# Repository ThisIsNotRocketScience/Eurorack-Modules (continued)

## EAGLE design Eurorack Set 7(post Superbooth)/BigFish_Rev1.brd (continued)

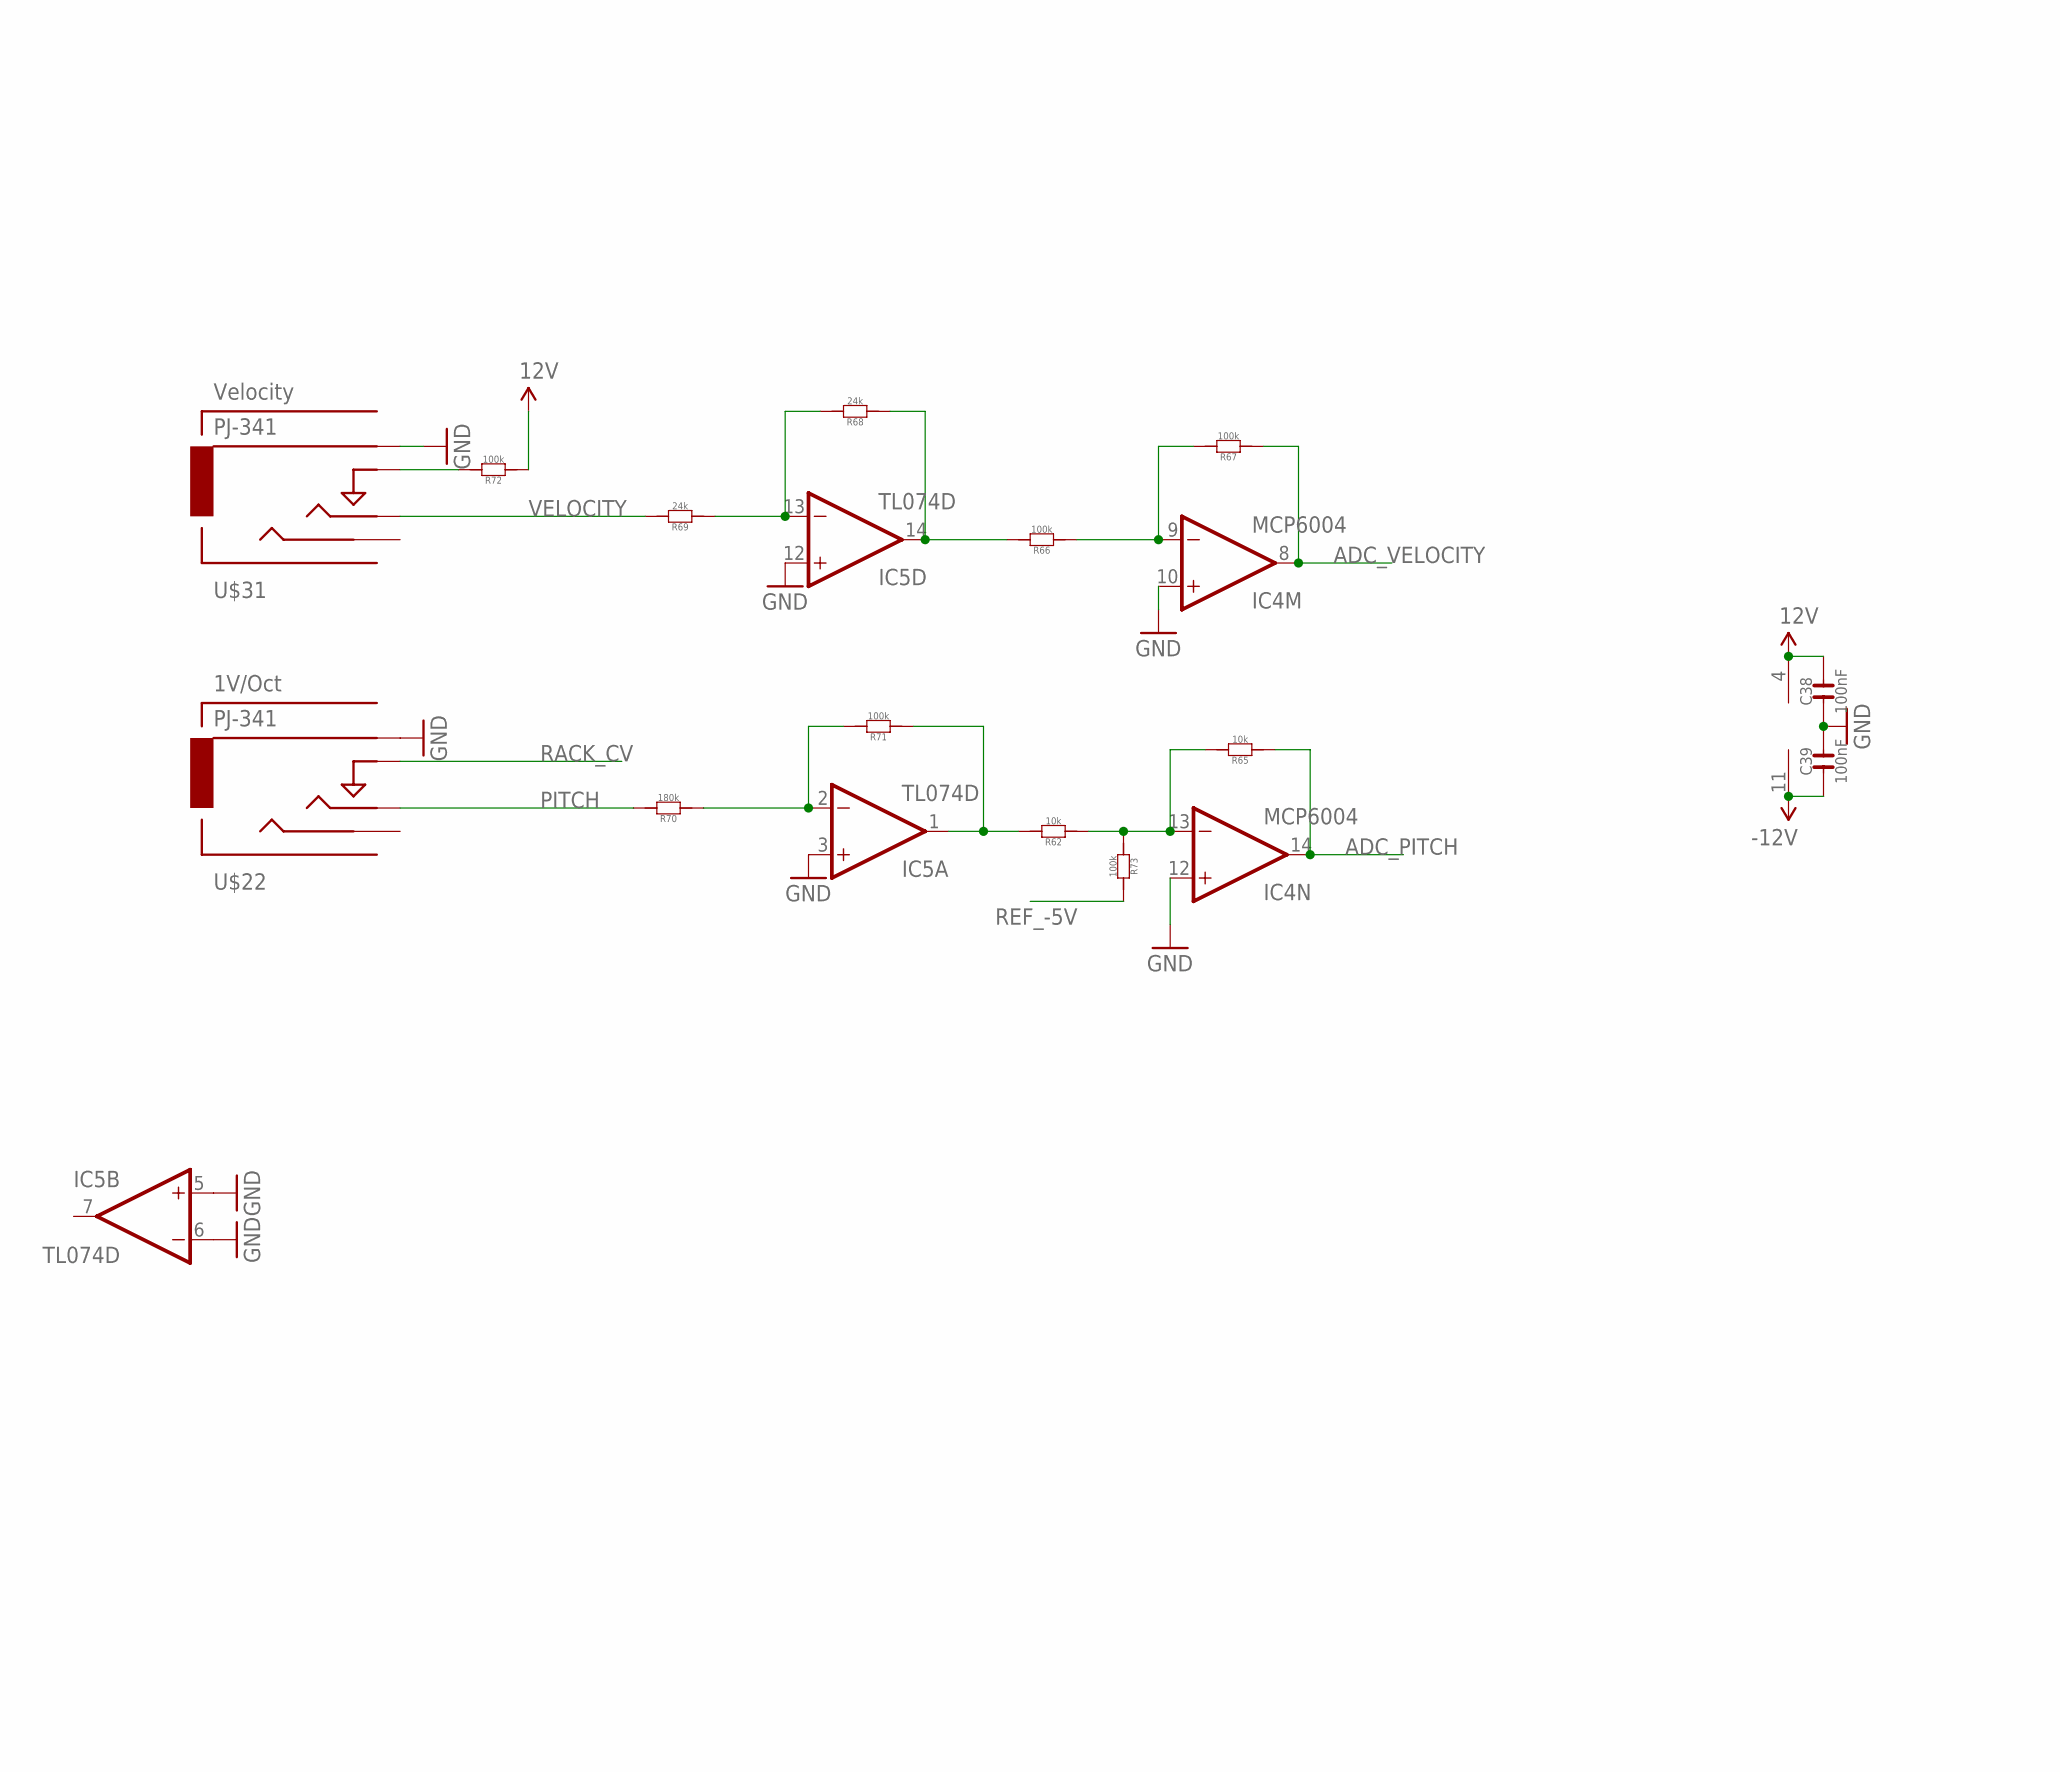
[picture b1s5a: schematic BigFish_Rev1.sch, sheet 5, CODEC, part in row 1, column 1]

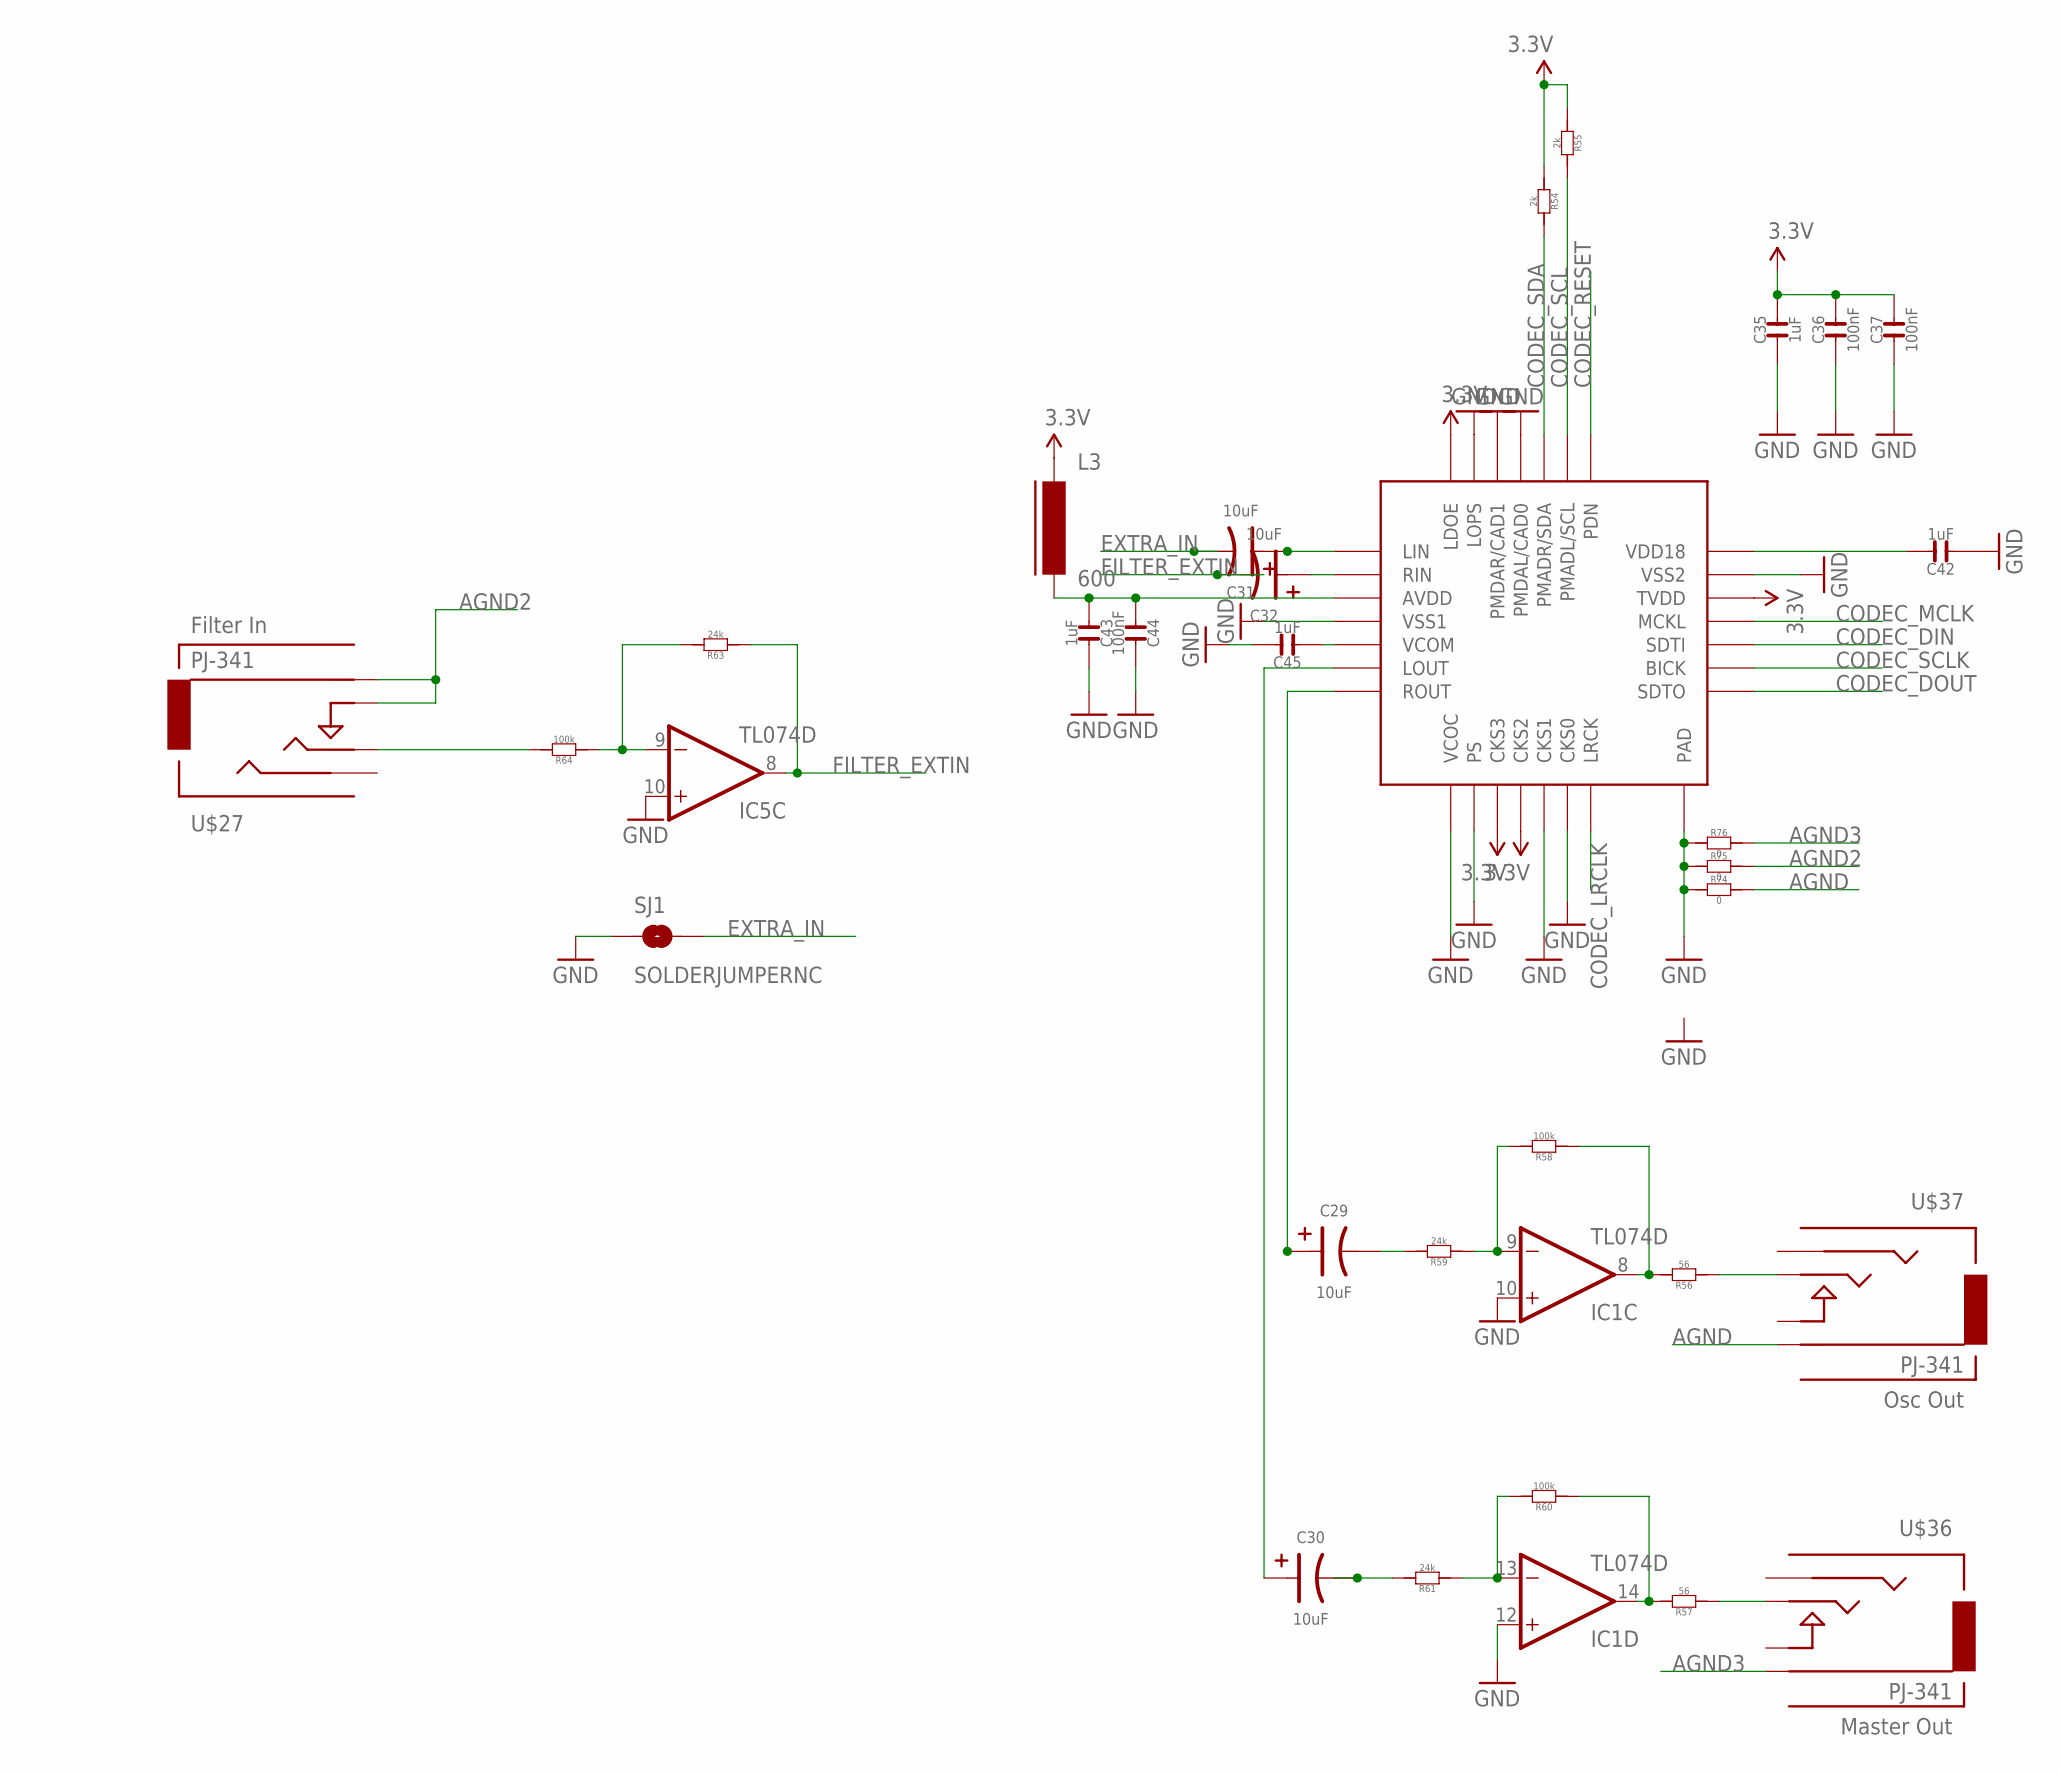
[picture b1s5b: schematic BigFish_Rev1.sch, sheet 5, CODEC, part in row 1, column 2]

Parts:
C29, C30, C31, C32: 10uF; AVX-A; MPN TAJB106K020RNJ
C35, C42, C43, C45: 1uF; C0603
C36, C37, C38, C39, C44: 100nF; C0603
IC1, IC5: TL074D; SO14
IC4: MCP6004; SO14; MPN MCP6004-I/SL.
L3: 600; FB603
R54, R55: 2k; R0603
R56, R57: 56; R0603
R58, R60, R64, R66, R67, R71, R72, R73: 100k; R0603
R59, R61, R63, R68, R69: 24k; R0603
R62, R65: 10k; R0603
R70: 180k; R0603
R74, R75, R76: 0; R0603
SJ1: SOLDERJUMPERNC; SJ_2S
U$22, U$27, U$31: PJ-341; 3.5MM-JACK-SWITCH-13MM-INPUT
U$36, U$37: PJ-341; 3.5MM-JACK-SWITCH-13MM-OUTPUT
U$48: AK4558; QFN28

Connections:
3.3V: C35.2, C36.2, C37.2, L3.1, R54.2, R55.2, U$48.P$3 (CKS3), U$48.P$4 (CKS2), U$48.P$12 (TVDD), U$48.P$21 (LDOE); also elsewhere on the board
3.3VAUDIO1: C43.1, C44.1, L3.2, U$48.P$24 (AVDD)
12V: C38.2, IC5.4 (V+), R72.1; also elsewhere on the board
-12V: C39.1, IC5.11 (V-); also elsewhere on the board
ADC_PITCH: IC4.14 (OUT), R65.1; also elsewhere on the board
ADC_VELOCITY: IC4.8 (OUT), R67.1; also elsewhere on the board
AGND: R74.1, U$37.RING@3 (RING)
AGND2: R75.1, U$27.RING@3 (RING), U$27.SWITCH@3 (SWITCH)
AGND3: R76.1, U$36.RING@3 (RING)
CODEC_DIN: U$48.P$10 (SDTI); also elsewhere on the board
CODEC_DOUT: U$48.P$8 (SDTO); also elsewhere on the board
CODEC_LRCLK: U$48.P$7 (LRCK); also elsewhere on the board
CODEC_MCLK: U$48.P$11 (MCKL); also elsewhere on the board
CODEC_RESET: U$48.P$15 (PDN); also elsewhere on the board
CODEC_SCL: R55.1, U$48.P$16 (PMADL/SCL); also elsewhere on the board
CODEC_SCLK: U$48.P$9 (BICK); also elsewhere on the board
CODEC_SDA: R54.1, U$48.P$17 (PMADR/SDA); also elsewhere on the board
EXTRA_IN: C31.- (2), SJ1.2
FILTER_EXTIN: C32.- (2), IC5.8 (OUT), R63.1
GND: C35.1, C36.1, C37.1, C38.1, C39.2, C42.1, C43.2, C44.2, C45.2, IC1.10 (+IN), IC1.12 (+IN), IC4.10 (+IN), IC4.12 (+IN), IC5.3 (+IN), IC5.5 (+IN), IC5.6 (-IN), IC5.10 (+IN), IC5.12 (+IN), R74.2, R75.2, R76.2, SJ1.1, U$22.RING@3 (RING), U$31.RING@3 (RING), U$48.P$1 (VCOC), U$48.P$2 (PS), U$48.P$5 (CKS1), U$48.P$6 (CKS0), U$48.P$13 (VSS2), U$48.P$18 (PMDAL/CAD0), U$48.P$19 (PMDAR/CAD1), U$48.P$20 (LOPS), U$48.P$25 (VSS1), U$48.PAD; also elsewhere on the board
unnamed: C32.+ (1), U$48.P$23 (RIN)
unnamed: C29.+ (1), U$48.P$28 (ROUT)
unnamed: C30.+ (1), U$48.P$27 (LOUT)
unnamed: C31.+ (1), U$48.P$22 (LIN)
unnamed: R64.2, U$27.TIP@3 (TIP)
unnamed: IC5.2 (-IN), R70.1, R71.2
unnamed: IC5.1 (OUT), R62.2, R71.1
unnamed: C30.- (2), R61.2
unnamed: IC1.8 (OUT), R56.2, R58.1
unnamed: IC1.14 (OUT), R57.2, R60.1
unnamed: IC1.13 (-IN), R60.2, R61.1
unnamed: IC5.13 (-IN), R68.2, R69.1
unnamed: R57.1, U$36.TIP@3 (TIP)
unnamed: C29.- (2), R59.2
unnamed: IC1.9 (-IN), R58.2, R59.1
unnamed: IC5.14 (OUT), R66.2, R68.1
unnamed: R56.1, U$37.TIP@3 (TIP)
unnamed: IC5.9 (-IN), R63.2, R64.1
unnamed: IC4.13 (-IN), R62.1, R65.2, R73.1
unnamed: IC4.9 (-IN), R66.1, R67.2
unnamed: R72.2, U$31.SWITCH@3 (SWITCH)
unnamed: C42.2, U$48.P$14 (VDD18)
unnamed: C45.1, U$48.P$26 (VCOM)
PITCH: R70.2, U$22.TIP@3 (TIP)
RACK_CV: U$22.SWITCH@3 (SWITCH); also elsewhere on the board
REF_-5V: R73.2; also elsewhere on the board
VELOCITY: R69.2, U$31.TIP@3 (TIP)

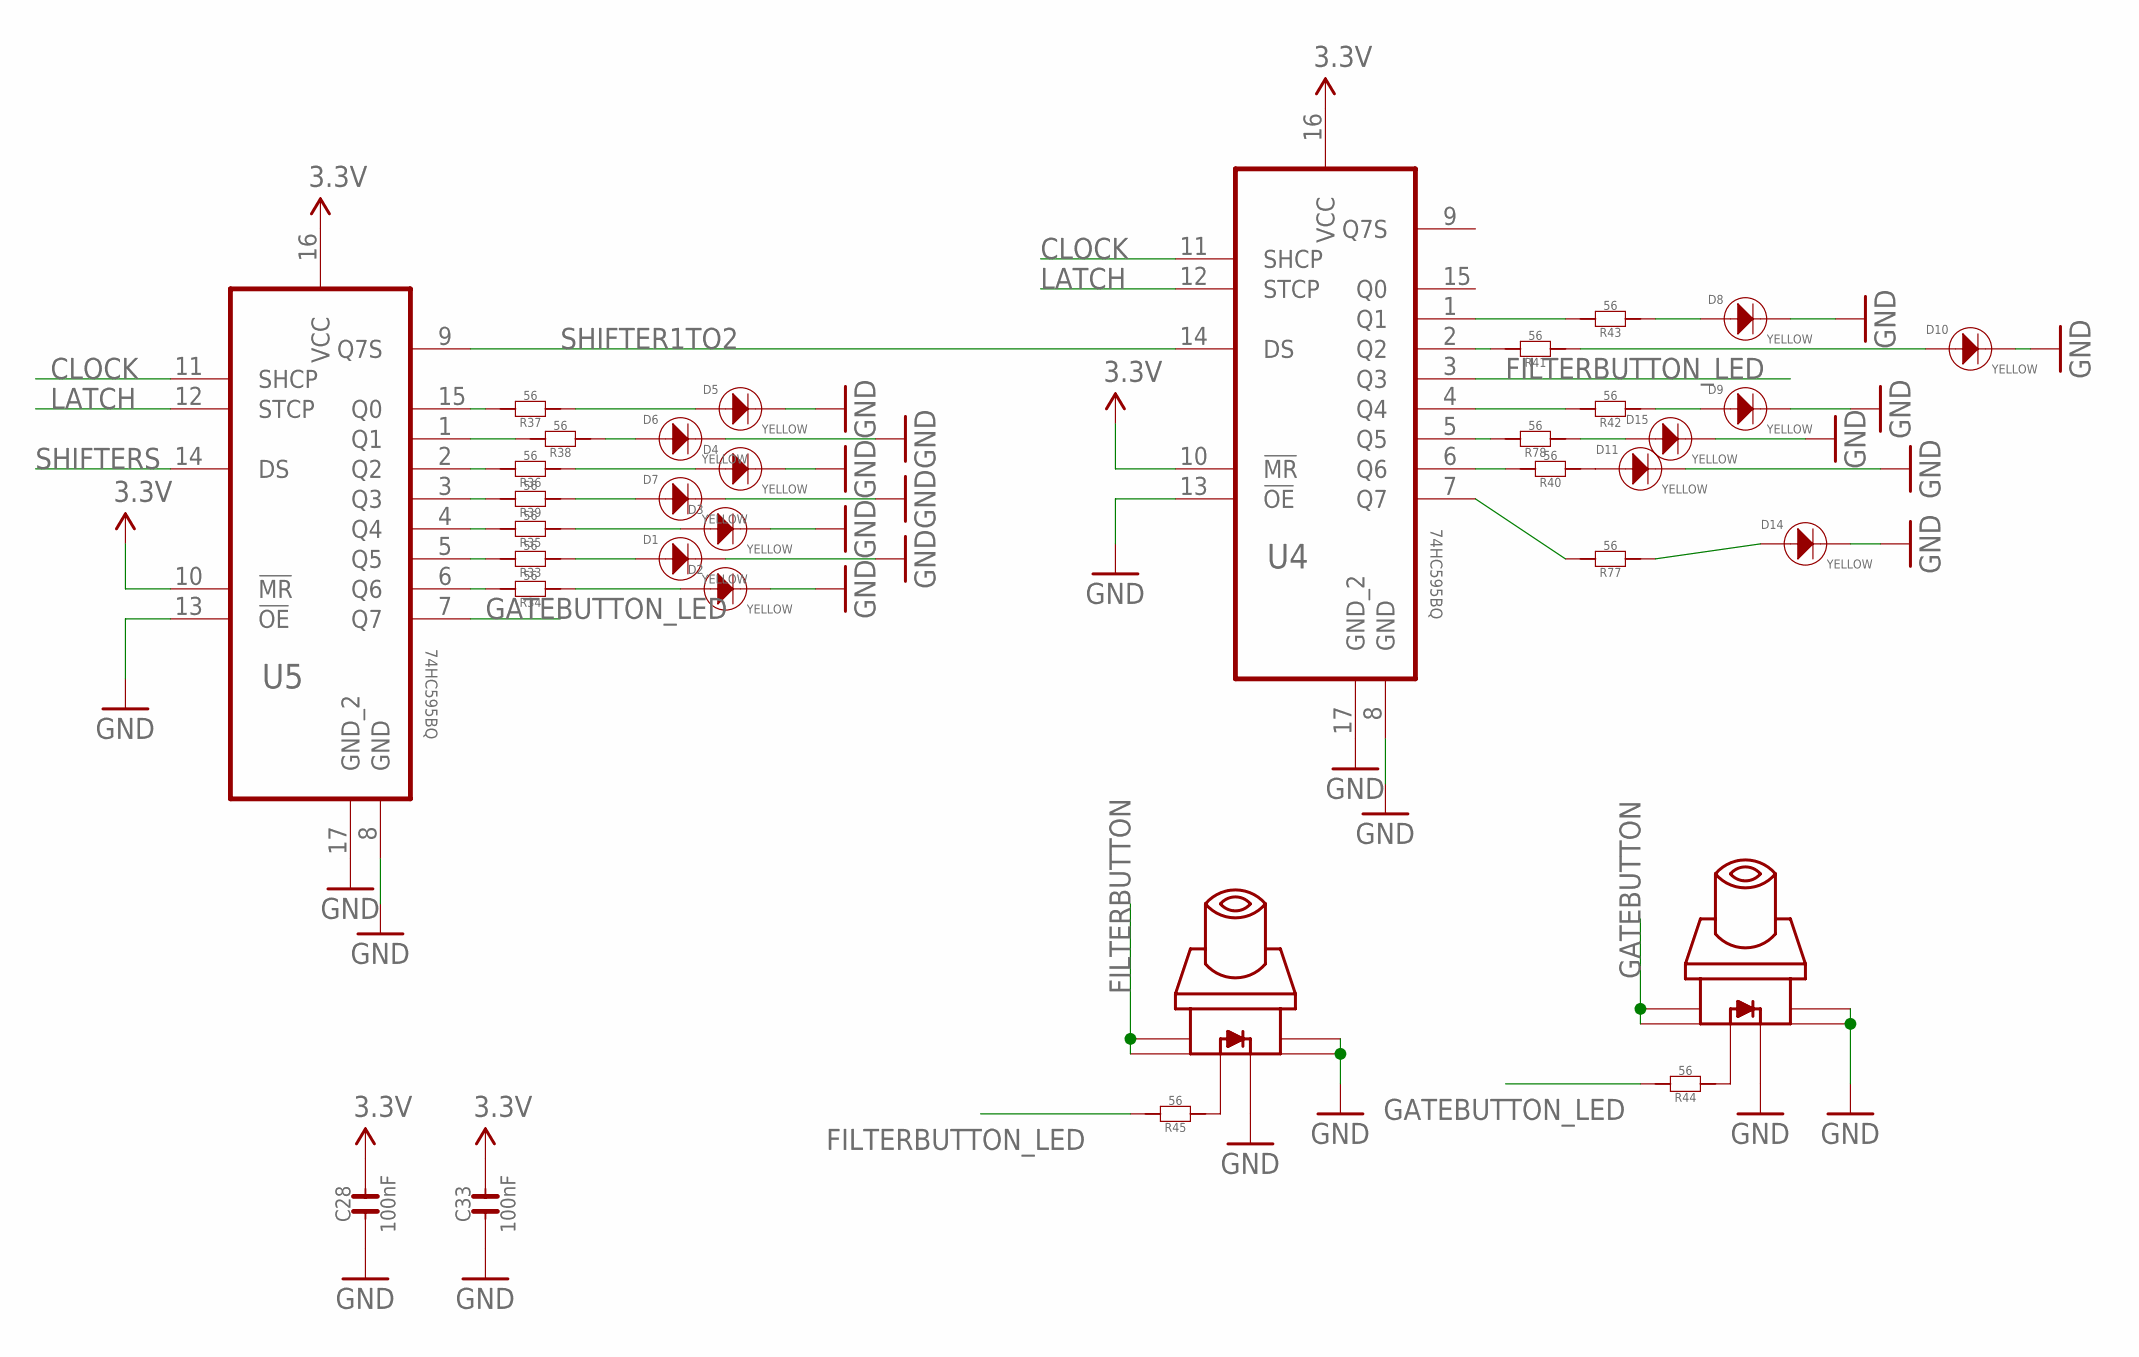
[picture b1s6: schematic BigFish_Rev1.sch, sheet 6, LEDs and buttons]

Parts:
C28, C33: 100nF; C0603
D1, D2, D3, D4, D5, D6, D7, D8, D9, D10, D11, D14, D15: YELLOW; LED0603
R33, R34, R35, R36, R37, R38, R39, R40, R41, R42, R43, R44, R45, R77, R78: 56; R0603
U4, U5: 74HC595BQ; QFN50P250X350X100-17N
U$38, U$39: SWITCH_W_LED_PB6149L-X-102YELLOW; PB6149L

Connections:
3.3V: C28.2, C33.2, U4.10 (!MR), U4.16 (VCC), U5.10 (!MR), U5.16 (VCC); also elsewhere on the board
CLOCK: U4.11 (SHCP), U5.11 (SHCP); also elsewhere on the board
FILTERBUTTON: U$39.1, U$39.2; also elsewhere on the board
FILTERBUTTON_LED: R45.2, U4.3 (Q3)
GATEBUTTON: U$38.1, U$38.2; also elsewhere on the board
GATEBUTTON_LED: R44.2, U5.7 (Q7)
GND: C28.1, C33.1, D1.-, D2.-, D3.-, D4.-, D5.-, D6.-, D7.-, D8.-, D9.-, D10.-, D11.-, D14.-, D15.-, U4.8 (GND), U4.13 (!OE), U4.17 (GND_2), U5.8 (GND), U5.13 (!OE), U5.17 (GND_2), U$38.3, U$38.4, U$38.LEDNEG (NEG), U$39.3, U$39.4, U$39.LEDNEG (NEG); also elsewhere on the board
LATCH: U4.12 (STCP), U5.12 (STCP); also elsewhere on the board
unnamed: D1.+, R33.1
unnamed: D2.+, R34.1
unnamed: D3.+, R35.1
unnamed: D4.+, R36.1
unnamed: D5.+, R37.1
unnamed: D6.+, R38.1
unnamed: D7.+, R39.1
unnamed: D11.+, R40.1
unnamed: D10.+, R41.1
unnamed: D9.+, R42.1
unnamed: D8.+, R43.1
unnamed: R44.1, U$38.LEDPOS (POS)
unnamed: R45.1, U$39.LEDPOS (POS)
unnamed: R34.2, U5.6 (Q6)
unnamed: R35.2, U5.4 (Q4)
unnamed: R33.2, U5.5 (Q5)
unnamed: R39.2, U5.3 (Q3)
unnamed: R36.2, U5.2 (Q2)
unnamed: R37.2, U5.15 (Q0)
unnamed: R38.2, U5.1 (Q1)
unnamed: R43.2, U4.1 (Q1)
unnamed: R42.2, U4.4 (Q4)
unnamed: R41.2, U4.2 (Q2)
unnamed: R40.2, U4.6 (Q6)
unnamed: D14.+, R77.1
unnamed: R77.2, U4.7 (Q7)
unnamed: R78.2, U4.5 (Q5)
unnamed: D15.+, R78.1
SHIFTER1TO2: U4.14 (DS), U5.9 (Q7S)
SHIFTERS: U5.14 (DS); also elsewhere on the board

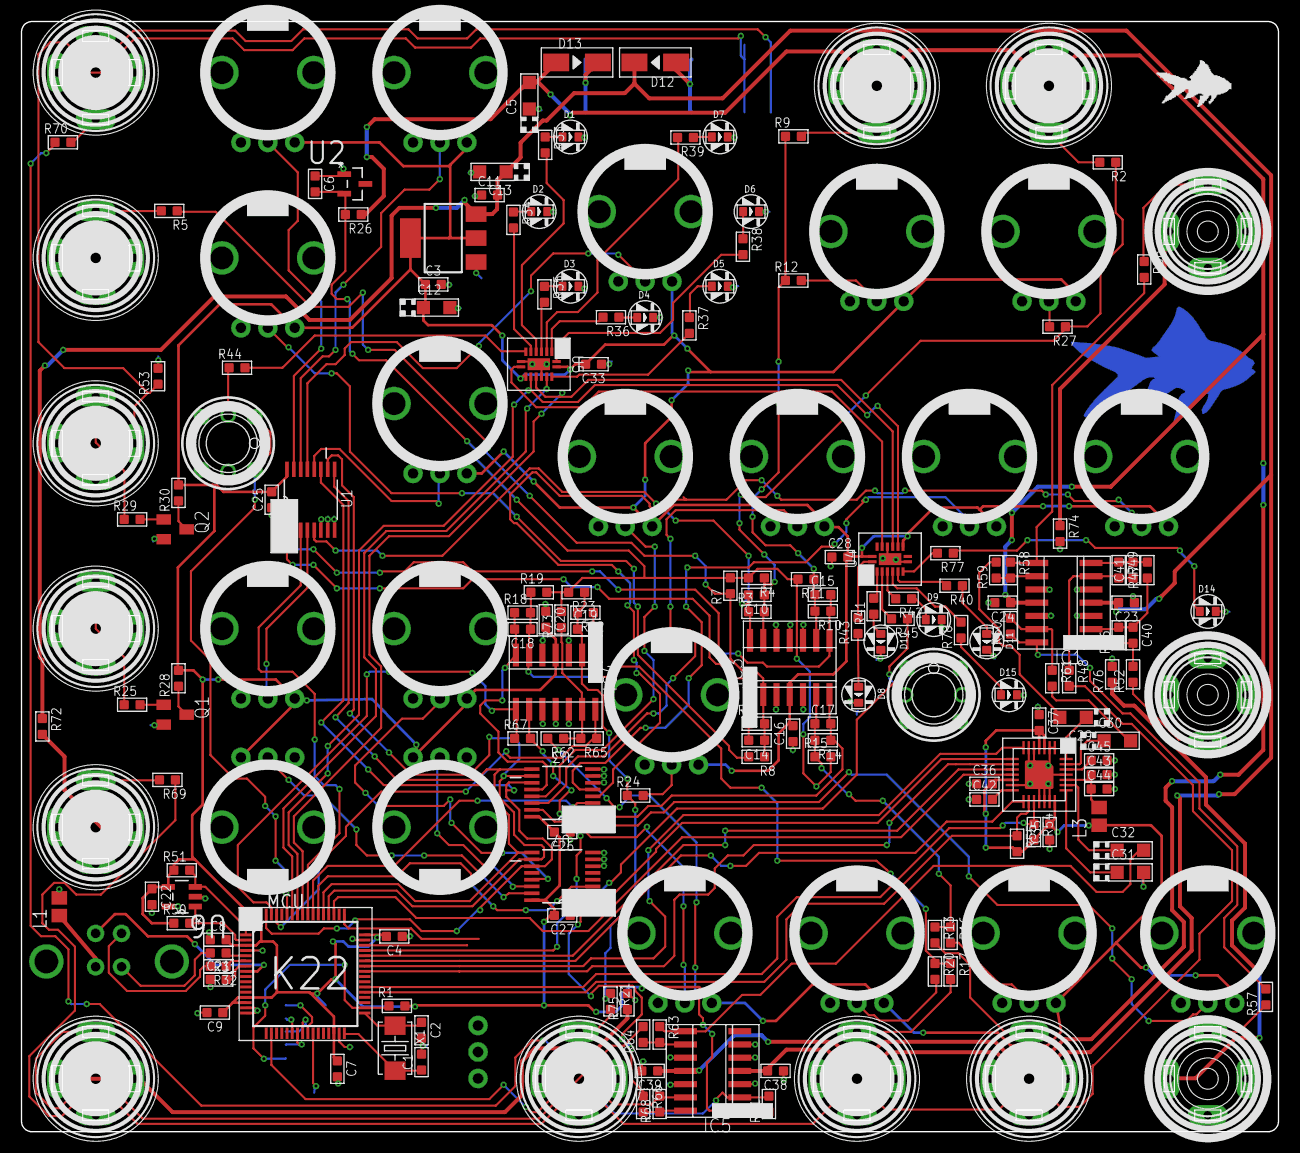
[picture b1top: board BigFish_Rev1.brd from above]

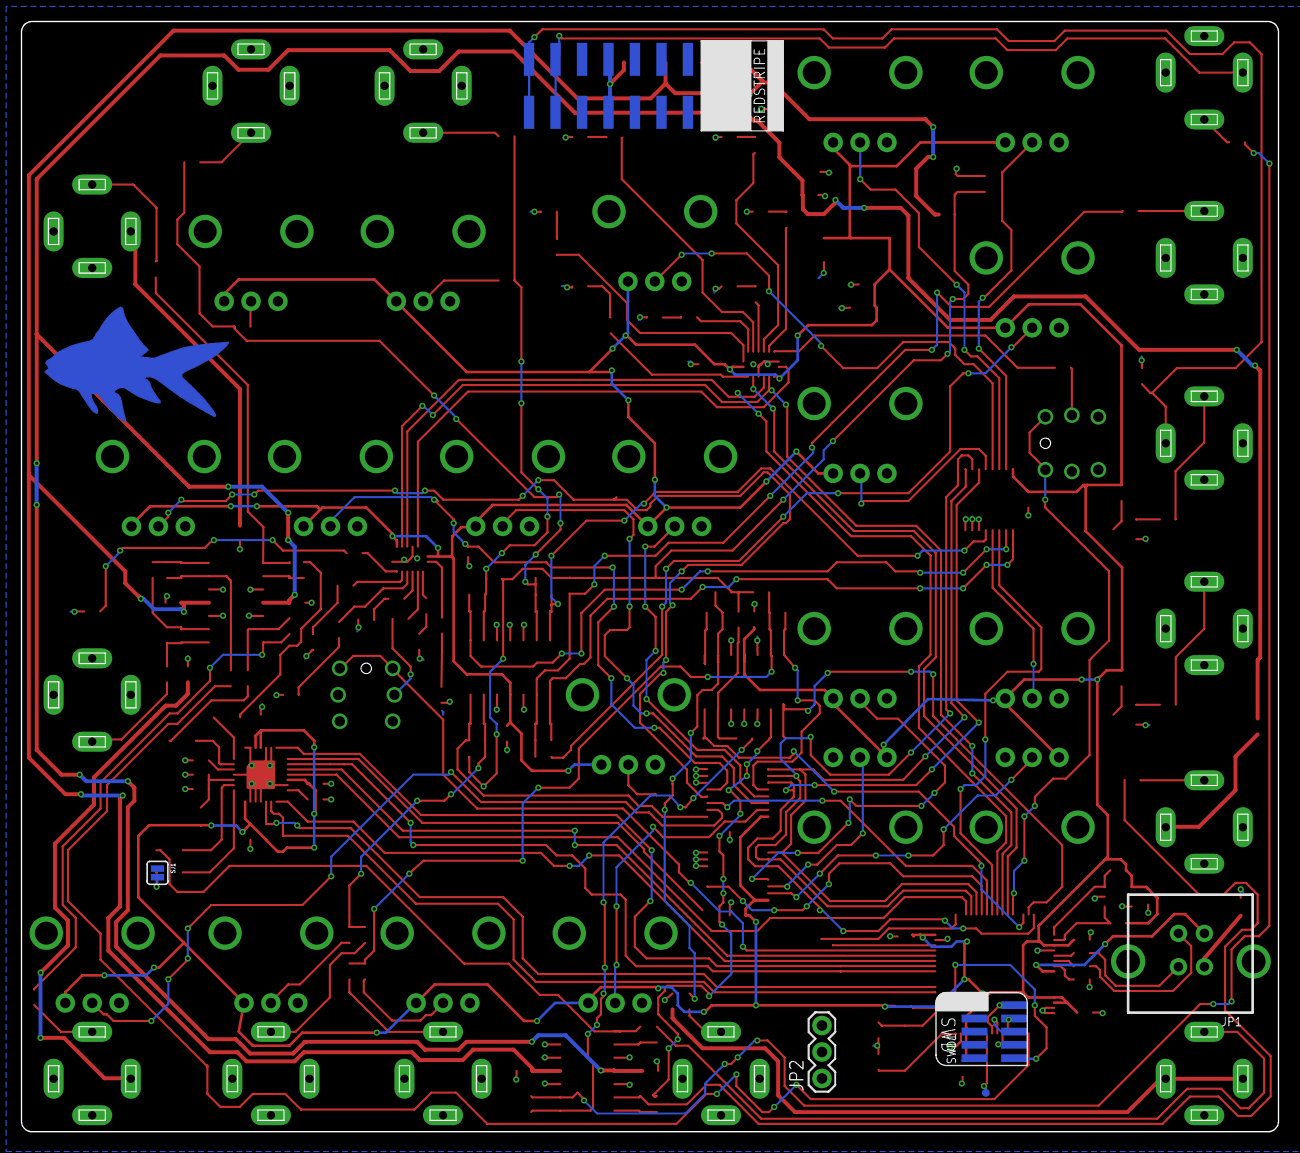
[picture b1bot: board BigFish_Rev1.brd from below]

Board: 2 copper layers, 120.6 x 106.5 mm, 201 parts (7 on the bottom side), 161 nets.

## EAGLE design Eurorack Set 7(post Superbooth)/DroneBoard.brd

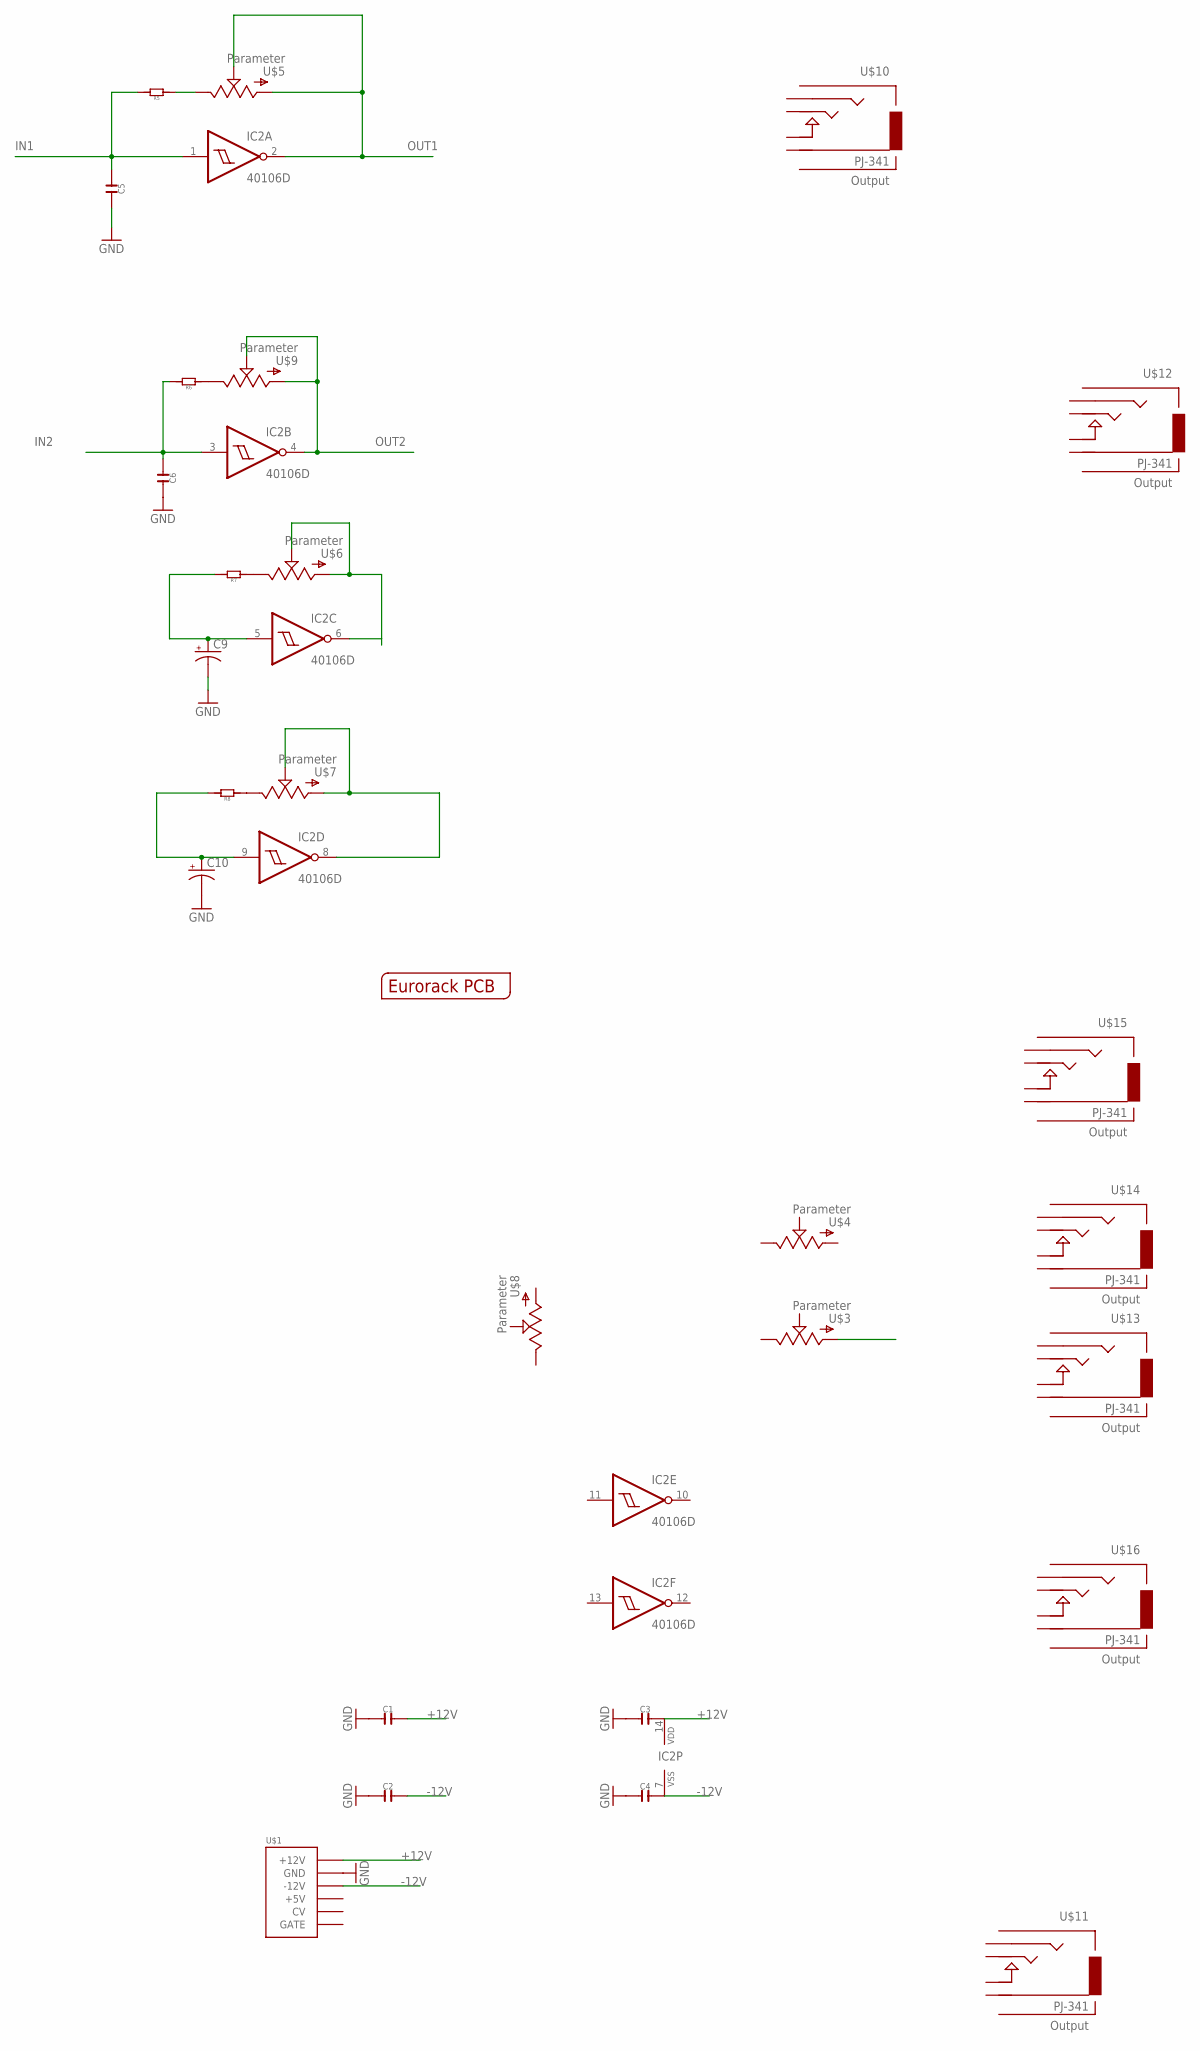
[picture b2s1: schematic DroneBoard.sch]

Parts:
C1, C2, C3, C4, C5, C6: C-0603; C0603
C9, C10: CPOL-US153CLV-0505; 153CLV-0505
IC2: 40106D; SO14
R5, R6, R7, R8: R-0603; R0603
U$1: POWERSHROUDED; POWER_16_SHROUDED
U$2: EURORACK_PCB8HP; EURORACK8HPPCB
U$3, U$4, U$5, U$6, U$7, U$8, U$9: POTZEPHPOT; OG-POTS_ALPS_POT_VERTICAL
U$10, U$11, U$12, U$13, U$14, U$15, U$16: PJ-341; 3.5MM-JACK-SWITCH-13MM-OUTPUT

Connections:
+12V: C1.2, C3.2, IC2.14 (VDD), U$1.9 (+12V), U$1.10 (+12V)
-12V: C2.2, C4.2, IC2.7 (VSS), U$1.1 (-12V), U$1.2 (-12V)
GND: C1.1, C2.1, C3.1, C4.1, C5.2, C6.2, C9.-, C10.-, U$1.3 (GND), U$1.4 (GND), U$1.5 (GND), U$1.6 (GND), U$1.7 (GND), U$1.8 (GND)
IN1: C5.1, IC2.1 (I), R5.2
IN2: C6.1, IC2.3 (I), R6.2
unnamed: C9.+, IC2.5 (I), R7.2
unnamed: IC2.8 (O), U$7.P$2 (S), U$7.P$3 (A)
unnamed: R5.1, U$5.P$1 (E)
unnamed: R6.1, U$9.P$1 (E)
unnamed: C10.+, IC2.9 (I), R8.2
unnamed: R7.1, U$6.P$1 (E)
unnamed: R8.1, U$7.P$1 (E)
unnamed: IC2.6 (O), U$6.P$2 (S), U$6.P$3 (A)
OUT1: IC2.2 (O), U$5.P$2 (S), U$5.P$3 (A)
OUT2: IC2.4 (O), U$9.P$2 (S), U$9.P$3 (A)

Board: 2 copper layers, 29 parts (1 on the bottom side), 15 nets, no tracks yet.
